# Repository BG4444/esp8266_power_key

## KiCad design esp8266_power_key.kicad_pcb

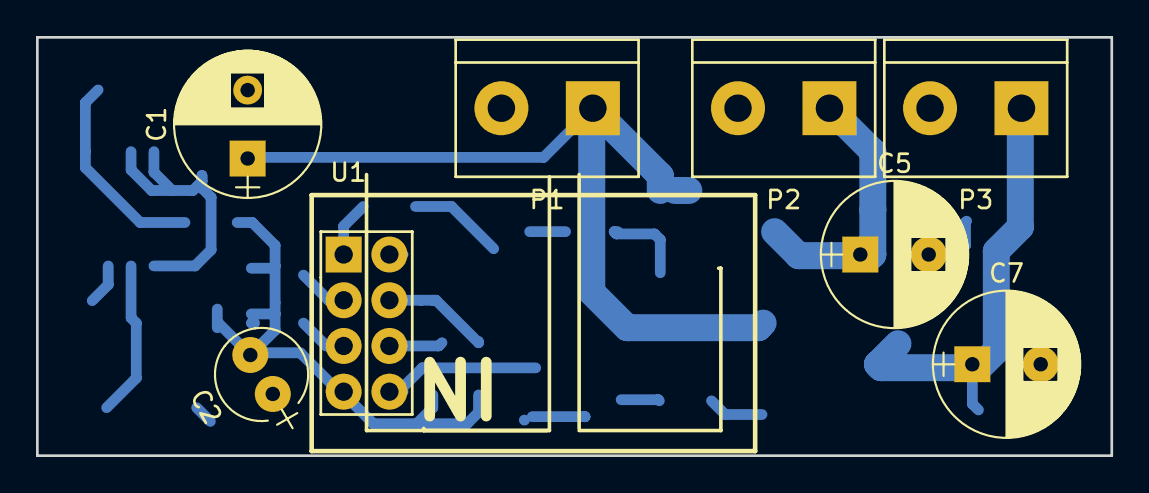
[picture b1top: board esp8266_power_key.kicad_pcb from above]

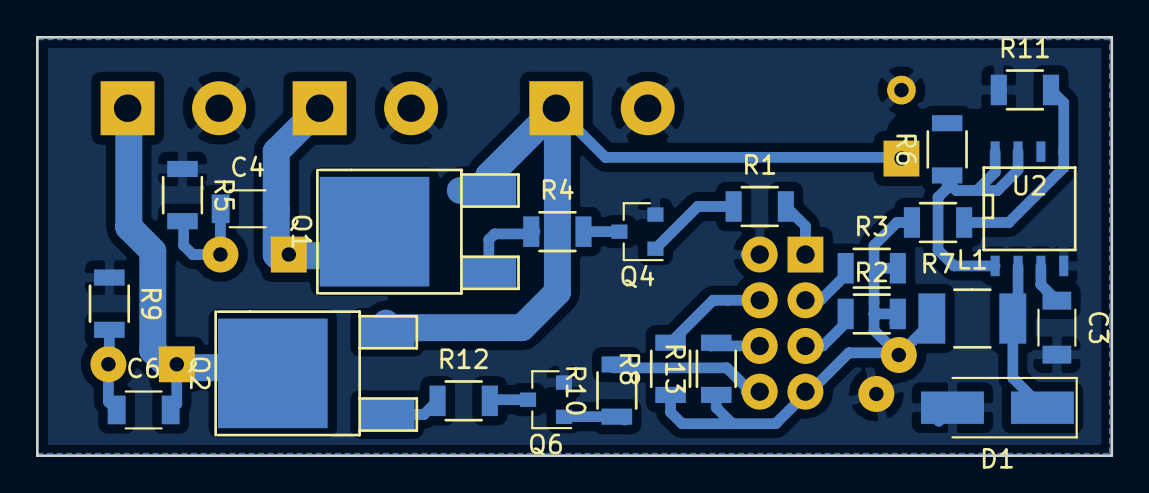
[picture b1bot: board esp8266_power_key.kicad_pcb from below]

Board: 2 copper layers, 59.7 x 23.2 mm, 31 parts (23 on the bottom side), 23 nets.

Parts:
C1, C5, C7: CP; CP_Radial_D8.0mm_P3.80mm
C2: CP; CP_Radial_Tantal_D5.0mm_P2.50mm
C3, C4, C6: C; C_1206
D1: D; D_SMA_Handsoldering
L1: INDUCTOR_SMALL; Neosid_Inductor_SM-NE45_SMD1812
P1, P2, P3: CONN_01X02; bornier2
Q1, Q2: Q_NMOS_GDS; TO-252-2Lead
Q4, Q6: BC849; SOT-23
R1, R2, R3, R4, R5, R6, R7, R8, R9, R10, R11, R12, R13: R; R_1206
U1: ESP-01v090; ESP-01
U2: LP2988AIMX-3.3/NOPB; SOIC-8-N

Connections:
+3V3: C2.2, L1.1, R2.2, R3.2, R7.2, R8.1, R13.1, U1.7
+36V: C1.1, P1.1, Q1.3, Q2.3, U2.6
GND: C1.2, C2.1, C3.2, D1.2, P1.2, P2.2, P3.2, Q4.2, Q6.2, R5.1, R9.1, R11.1, U1.2, U2.4
unnamed: C3.1, U2.3
unnamed: C4.1, C5.2, R5.2
unnamed: C4.2, C5.1, P2.1, Q1.2
unnamed: C6.1, C7.2, R9.2
unnamed: C6.2, C7.1, P3.1, Q2.2
unnamed: D1.1, L1.2, U2.2
unnamed: Q1.1, R4.1
unnamed: Q2.1, R12.1
unnamed: Q4.1, R1.1
unnamed: Q4.3, R4.2
unnamed: Q6.1, R10.1
unnamed: Q6.3, R12.2
unnamed: R1.2, U1.1
unnamed: R2.1, U1.5
unnamed: R3.1, U1.3
unnamed: R6.1, U2.1, U2.7, U2.8
unnamed: R8.2, U1.4
unnamed: R10.2, U1.8
unnamed: R7.1, R11.2, U2.5
unnamed: R13.2, U1.6

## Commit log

2016-12-06 initial blinky example
2016-12-06 transformed to working example (WiFi client + tcp client)
2016-12-06 removed extra code
2016-12-06 first working prototype - led is controlable
2016-12-10 Merged kicad-ESP8266 as our subdirectory
2016-12-14 Rev 1_0 2 key 2 button
2016-12-21 4 channel version
2016-12-21 moved corners
2016-12-28 changed size
2017-01-16 Rev 2.0
2017-01-16 resaved
2017-01-18 last save
2017-01-18 topology fix
2017-01-18 minor fixes
2017-11-19 *telnet 1-2 version*
2017-12-31 *long poll now working
2018-01-03 *FIXED LONG POLL
2018-10-06 bughunting with append
2018-10-06 add log clean on query
